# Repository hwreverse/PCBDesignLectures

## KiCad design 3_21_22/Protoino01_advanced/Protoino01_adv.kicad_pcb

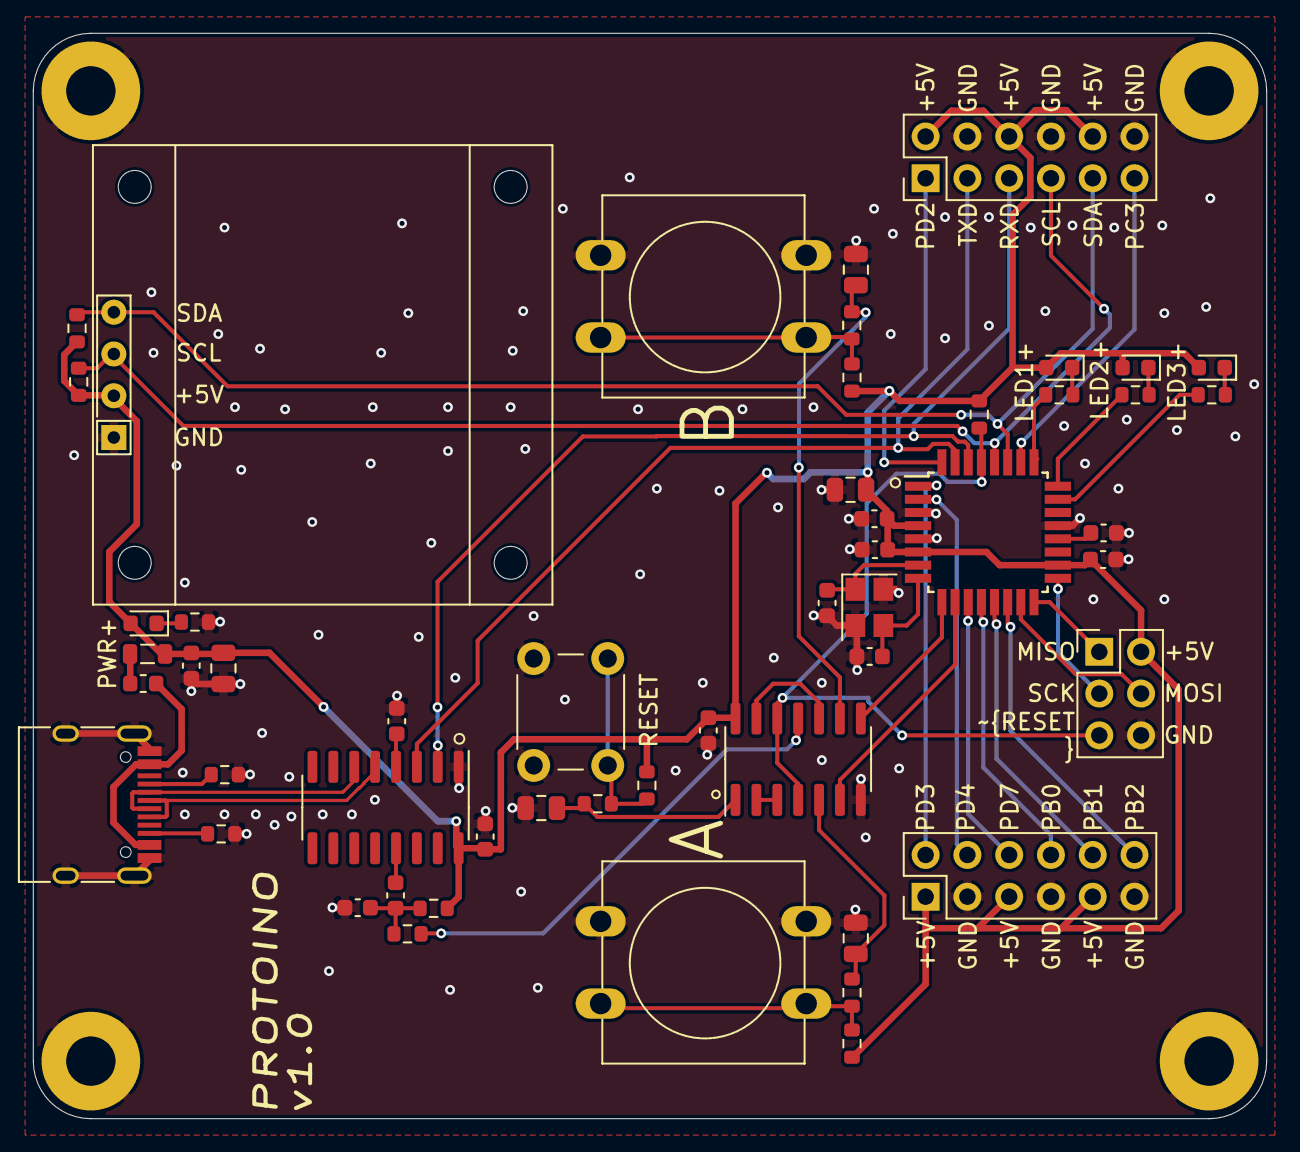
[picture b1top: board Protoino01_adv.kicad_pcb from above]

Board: 2 copper layers, 75.0 x 66.0 mm, 56 parts (0 on the bottom side), 48 nets.

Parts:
C1, C2, C4, C7, C9, C10, C11, C17: 100nF; C_0603_1608Metric
C3, C8, C12, C15, C16: 10uF; C_0805_2012Metric
C5, C6: 15pF; C_0603_1608Metric
C13, C14: 1uF; C_0603_1608Metric
D1: PWR_Blue; LED_0603_1608Metric
D2: LED_RED; LED_0603_1608Metric
D3: LED_Yellow; LED_0603_1608Metric
D4: LED_Green; LED_0603_1608Metric
F1: 700mA; Fuse_0603_1608Metric
FB1: Ferrite_Bead_Small; L_0805_2012Metric
H1, H2, H3, H4: MountingHole_Pad; MountingHole_3mm_Pad
J1: USB_C_Receptacle_USB2.0; USB_C_Receptacle_HRO_TYPE-C-31-M-12
J2: ICSP; PinHeader_2x03_P2.54mm_Vertical
J3, J4: Conn_02x06_Odd_Even; PinHeader_2x06_P2.54mm_Vertical
OLED1: I2C_OLED_128x64; OLED_I2C_128x64
R1, R2: 4.7K; R_0603_1608Metric
R3, R4: 5.1K; R_0603_1608Metric
R5: 2.2K; R_0603_1608Metric
R6, R7, R8, R9, R11, R12, R13, R14: 10K; R_0603_1608Metric
R10: 100R; R_0603_1608Metric
R15, R16, R17: ?K; R_0603_1608Metric
SW1: RESET; SW_PUSH_6mm
SW2: SW1; SW_PUSH-12mm
SW3: SW2; SW_PUSH-12mm
U1: ATmega328P-AU; TQFP-32_7x7mm_P0.8mm
U2: CH340C; SOIC-16_3.9x9.9mm_P1.27mm
U3: 74HC14; SOIC-14_3.9x8.7mm_P1.27mm
Y1: 16MHz; Crystal_SMD_3225-4Pin_3.2x2.5mm

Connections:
+5V: C2.1, C3.1, C7.1, C8.1, C9.1, C10.1, C11.1, C17.1, D1.2, D2.2, D3.2, D4.2, FB1.1, J2.2, J3.1, J3.5, J3.9, J4.2, J4.6, J4.10, OLED1.2, R1.1, R2.1, R6.2, R7.2, R9.2, R11.2, R12.2, U1.4, U1.6, U1.18, U2.16, U3.14
/IDTR: R10.2, U3.11
/IRES: C12.1, R8.2, U3.1
/S1: C15.1, R13.2, U3.5
/S2: C16.1, R14.2, U3.9
D+: J1.A6, J1.B6, U2.5
D-: J1.A7, J1.B7, U2.6
DTR: C13.2, U2.13
GND: C1.2, C2.2, C3.2, C4.2, C5.2, C6.2, C7.2, C8.2, C9.2, C10.2, C11.2, C12.2, C14.1, C15.2, C16.2, C17.2, H1.1, H2.1, H3.1, H4.1, J1.A1, J1.A12, J1.B1, J1.B12, J1.S1, J2.6, J3.3, J3.7, J3.11, J4.4, J4.8, J4.12, OLED1.1, R3.1, R4.1, R5.1, SW1.1, SW2.1, SW3.1, U1.3, U1.5, U1.21, U2.1, U3.7, Y1.2, Y1.4
LED1: R15.1, U1.25
LED2: R16.1, U1.24
LED3: R17.1, U1.23
MISO: J2.1, U1.16
MOSI: J2.4, U1.15
unnamed: C1.1, U1.20
unnamed: C4.1, U2.4
unnamed: C13.1, C14.2, R9.1, R10.1
unnamed: D1.1, R5.2
unnamed: D2.1, R15.2
unnamed: D3.1, R16.2
unnamed: D4.1, R17.2
unnamed: F1.1, FB1.2
unnamed: F1.2, J1.A4, J1.A9, J1.B4, J1.B9
unnamed: J1.A5, R3.2
unnamed: J1.B5, R4.2
unnamed: R6.1, R8.1, SW1.2
unnamed: R11.1, R13.1, SW2.2
unnamed: R12.1, R14.1, SW3.2
unnamed: U3.2, U3.3
unnamed: U3.10, U3.13
OSC1: C5.1, U1.7, Y1.1
OSC2: C6.1, U1.8, Y1.3
PB0: J3.8, U1.12
PB1: J3.10, U1.13
PB2: J3.12, U1.14
PC3: J4.11, U1.26
PD2: J4.1, U1.32
PD3: J3.2, U1.1
PD4: J3.4, U1.2
PD7: J3.6, U1.11
RXD: J4.5, U1.30, U2.2
SCK: J2.3, U1.17
SCL: J4.7, OLED1.3, R1.2, U1.28
SDA: J4.9, OLED1.4, R2.2, U1.27
SW1: U1.10, U3.6
SW2: U1.9, U3.8
TXD: J4.3, U1.31, U2.3
~RESET: J2.5, R7.1, U1.29, U3.4, U3.12

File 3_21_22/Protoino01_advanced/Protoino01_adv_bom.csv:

Comment,Designator,Footprint,LCSC
"15pF","C6,C5","Capacitor_SMD:C_0603_1608Metric",""
"74HC14","U3","Package_SO:SOIC-14_3.9x8.7mm_P1.27mm",""
"4.7K","R1,R2","Resistor_SMD:R_0603_1608Metric",""
"16MHz","Y1","Crystal:Crystal_SMD_3225-4Pin_3.2x2.5mm",""
"MountingHole_Pad","H2,H3,H1,H4","MountingHole:MountingHole_3mm_Pad",""
"Conn_02x06_Odd_Even","J4,J3","Connector_PinHeader_2.54mm:PinHeader_2x06_P2.54mm_Vertical",""
"100nF","C17,C9,C2,C1,C10,C7,C11,C4","Capacitor_SMD:C_0603_1608Metric",""
"ATmega328P-AU","U1","Package_QFP:TQFP-32_7x7mm_P0.8mm",""
"SW1","SW2","Button_Switch_THT:SW_PUSH-12mm",""
"10uF","C3,C12,C8,C16,C15","Capacitor_SMD:C_0805_2012Metric",""
"USB_C_Receptacle_USB2.0","J1","Connector_USB:USB_C_Receptacle_HRO_TYPE-C-31-M-12",""
"RESET","SW1","Button_Switch_THT:SW_PUSH_6mm",""
"LED_RED","D2","LED_SMD:LED_0603_1608Metric",""
"700mA","F1","Fuse:Fuse_0603_1608Metric",""
"2.2K","R5","Resistor_SMD:R_0603_1608Metric",""
"?K","R16,R17,R15","Resistor_SMD:R_0603_1608Metric",""
"5.1K","R4,R3","Resistor_SMD:R_0603_1608Metric",""
"ICSP","J2","Connector_PinHeader_2.54mm:PinHeader_2x03_P2.54mm_Vertical",""
"PWR_Blue","D1","LED_SMD:LED_0603_1608Metric",""
"LED_Green","D4","LED_SMD:LED_0603_1608Metric",""
"LED_Yellow","D3","LED_SMD:LED_0603_1608Metric",""
"CH340C","U2","Package_SO:SOIC-16_3.9x9.9mm_P1.27mm",""
"I2C_OLED_128x64","OLED1","IU10b:OLED_I2C_128x64",""
"Ferrite_Bead_Small","FB1","Inductor_SMD:L_0805_2012Metric",""
"1uF","C13,C14","Capacitor_SMD:C_0603_1608Metric",""
"SW2","SW3","Button_Switch_THT:SW_PUSH-12mm",""
"10K","R6,R7,R12,R13,R11,R8,R14,R9","Resistor_SMD:R_0603_1608Metric",""
"100R","R10","Resistor_SMD:R_0603_1608Metric",""
